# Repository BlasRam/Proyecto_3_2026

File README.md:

# Sistema Experimental para el Monitoreo de la Calidad del Aire Interior (IAQ) y Variables Ambientales con Comunicación LoRa

## Descripción

Este repositorio contiene el desarrollo de un sistema experimental para el monitoreo de la calidad del aire interior (IAQ) y variables ambientales, con capacidad de comunicación inalámbrica mediante tecnología LoRa.

El proyecto está orientado al diseño y validación de una plataforma electrónica basada en **ESP32-S3**, integrando sensado ambiental, adquisición de señales, supervisión energética y transmisión de datos. La propuesta busca servir como base para futuras pruebas de hardware, adquisición de datos ambientales y validación de un sistema completo de monitoreo IAQ.

## Objetivo

Desarrollar una plataforma experimental capaz de:

- monitorear variables asociadas a la calidad del aire interior
- adquirir variables ambientales complementarias
- supervisar el estado energético del sistema
- transmitir información de manera inalámbrica mediante LoRa
- servir como base para futuras etapas de validación y escalabilidad

## Características principales

- Microcontrolador **ESP32-S3**
- Monitoreo de calidad del aire interior (**IAQ**)
- Medición de variables ambientales
- Comunicación **LoRa**
- Supervisión de batería y alimentación
- Diseño electrónico propio en desarrollo
- Arquitectura modular y escalable

## Estado del proyecto

Actualmente el proyecto se encuentra en etapa de:

- desarrollo del esquemático electrónico
- selección e integración de componentes
- definición de arquitectura de alimentación y comunicaciones
- preparación para diseño de PCB
- consolidación del prototipo experimental

## Arquitectura general

El sistema contempla los siguientes bloques principales:

- **Unidad de control:** ESP32-S3
- **Sensado ambiental e IAQ:** sensores para calidad del aire y variables ambientales
- **Comunicación inalámbrica:** módulo LoRa
- **Supervisión energética:** monitoreo de batería y consumo
- **Alimentación:** entrada USB, batería recargable y regulación de voltaje
- **Expansión:** puertos auxiliares para futuras integraciones

## Tecnologías y módulos considerados

Dependiendo de la iteración del prototipo, el sistema contempla o evalúa componentes como:

- **ESP32-S3-WROOM-1**
- **RFM95CW** o **RYLR998** para comunicación LoRa
- **ENS160 / AHT2X** para IAQ y variables ambientales
- **ADS1015** para adquisición analógica adicional
- **MAX17048** para monitoreo de batería
- **TP4056** para carga de batería
- reguladores de 3.3 V para alimentación estable del sistema

## Estructura del repositorio

```text
/
├── Software/          # Programacion (Codigos y Pruebas) del proyecto
├── docs/              # Documentación del proyecto
├── hardware/          # Esquemáticos, PCB, librerías y archivos de diseño
├── firmware/          # Código fuente del microcontrolador
├── images/            # Diagramas, capturas y recursos gráficos
├── datasheets/        # Hojas de datos de los componentes utilizados
└── README.md          # Descripción general del proyecto

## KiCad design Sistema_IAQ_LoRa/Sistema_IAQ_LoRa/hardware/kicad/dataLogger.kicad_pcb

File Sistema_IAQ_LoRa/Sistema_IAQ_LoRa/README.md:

# Sistema Experimental para el Monitoreo de la Calidad del Aire Interior (IAQ) y Variables Ambientales con Comunicación LoRa

## Descripción
Este repositorio contiene el desarrollo de un sistema experimental para el monitoreo de la calidad del aire interior (IAQ) y variables ambientales, con capacidad de comunicación inalámbrica mediante tecnología LoRa.

El proyecto está orientado al diseño y validación de una plataforma electrónica basada en ESP32-S3, integrando sensado ambiental, adquisición de señales, supervisión energética y transmisión de datos. La propuesta busca servir como base para futuras pruebas de hardware, adquisición de datos ambientales y validación de un sistema completo de monitoreo IAQ.

## Estructura del repositorio
```text
.
├── docs/                # Documentación del proyecto
├── hardware/            # Esquemáticos, PCB, librerías y archivos de fabricación
│   ├── kicad/           # Proyecto principal de KiCad
│   ├── libraries/       # Footprints, símbolos y modelos 3D adicionales
│   └── manufacturing/   # Archivos de producción (Gerbers, BOM, posiciones, etc.)
├── firmware/            # Código fuente del microcontrolador
├── images/              # Diagramas, capturas y recursos gráficos
├── datasheets/          # Hojas de datos de los componentes utilizados
└── README.md            # Descripción general del proyecto
```

## Integrantes
- Blas Antonio Ramirez Benitez
- Pedro Daniel Vera Ramirez
- Pablo Junior Otazu Lujan

## Estado del proyecto
Actualmente el proyecto se encuentra en etapa de desarrollo del prototipo electrónico, consolidación del esquemático y organización de los archivos de diseño para futuras pruebas y fabricación.

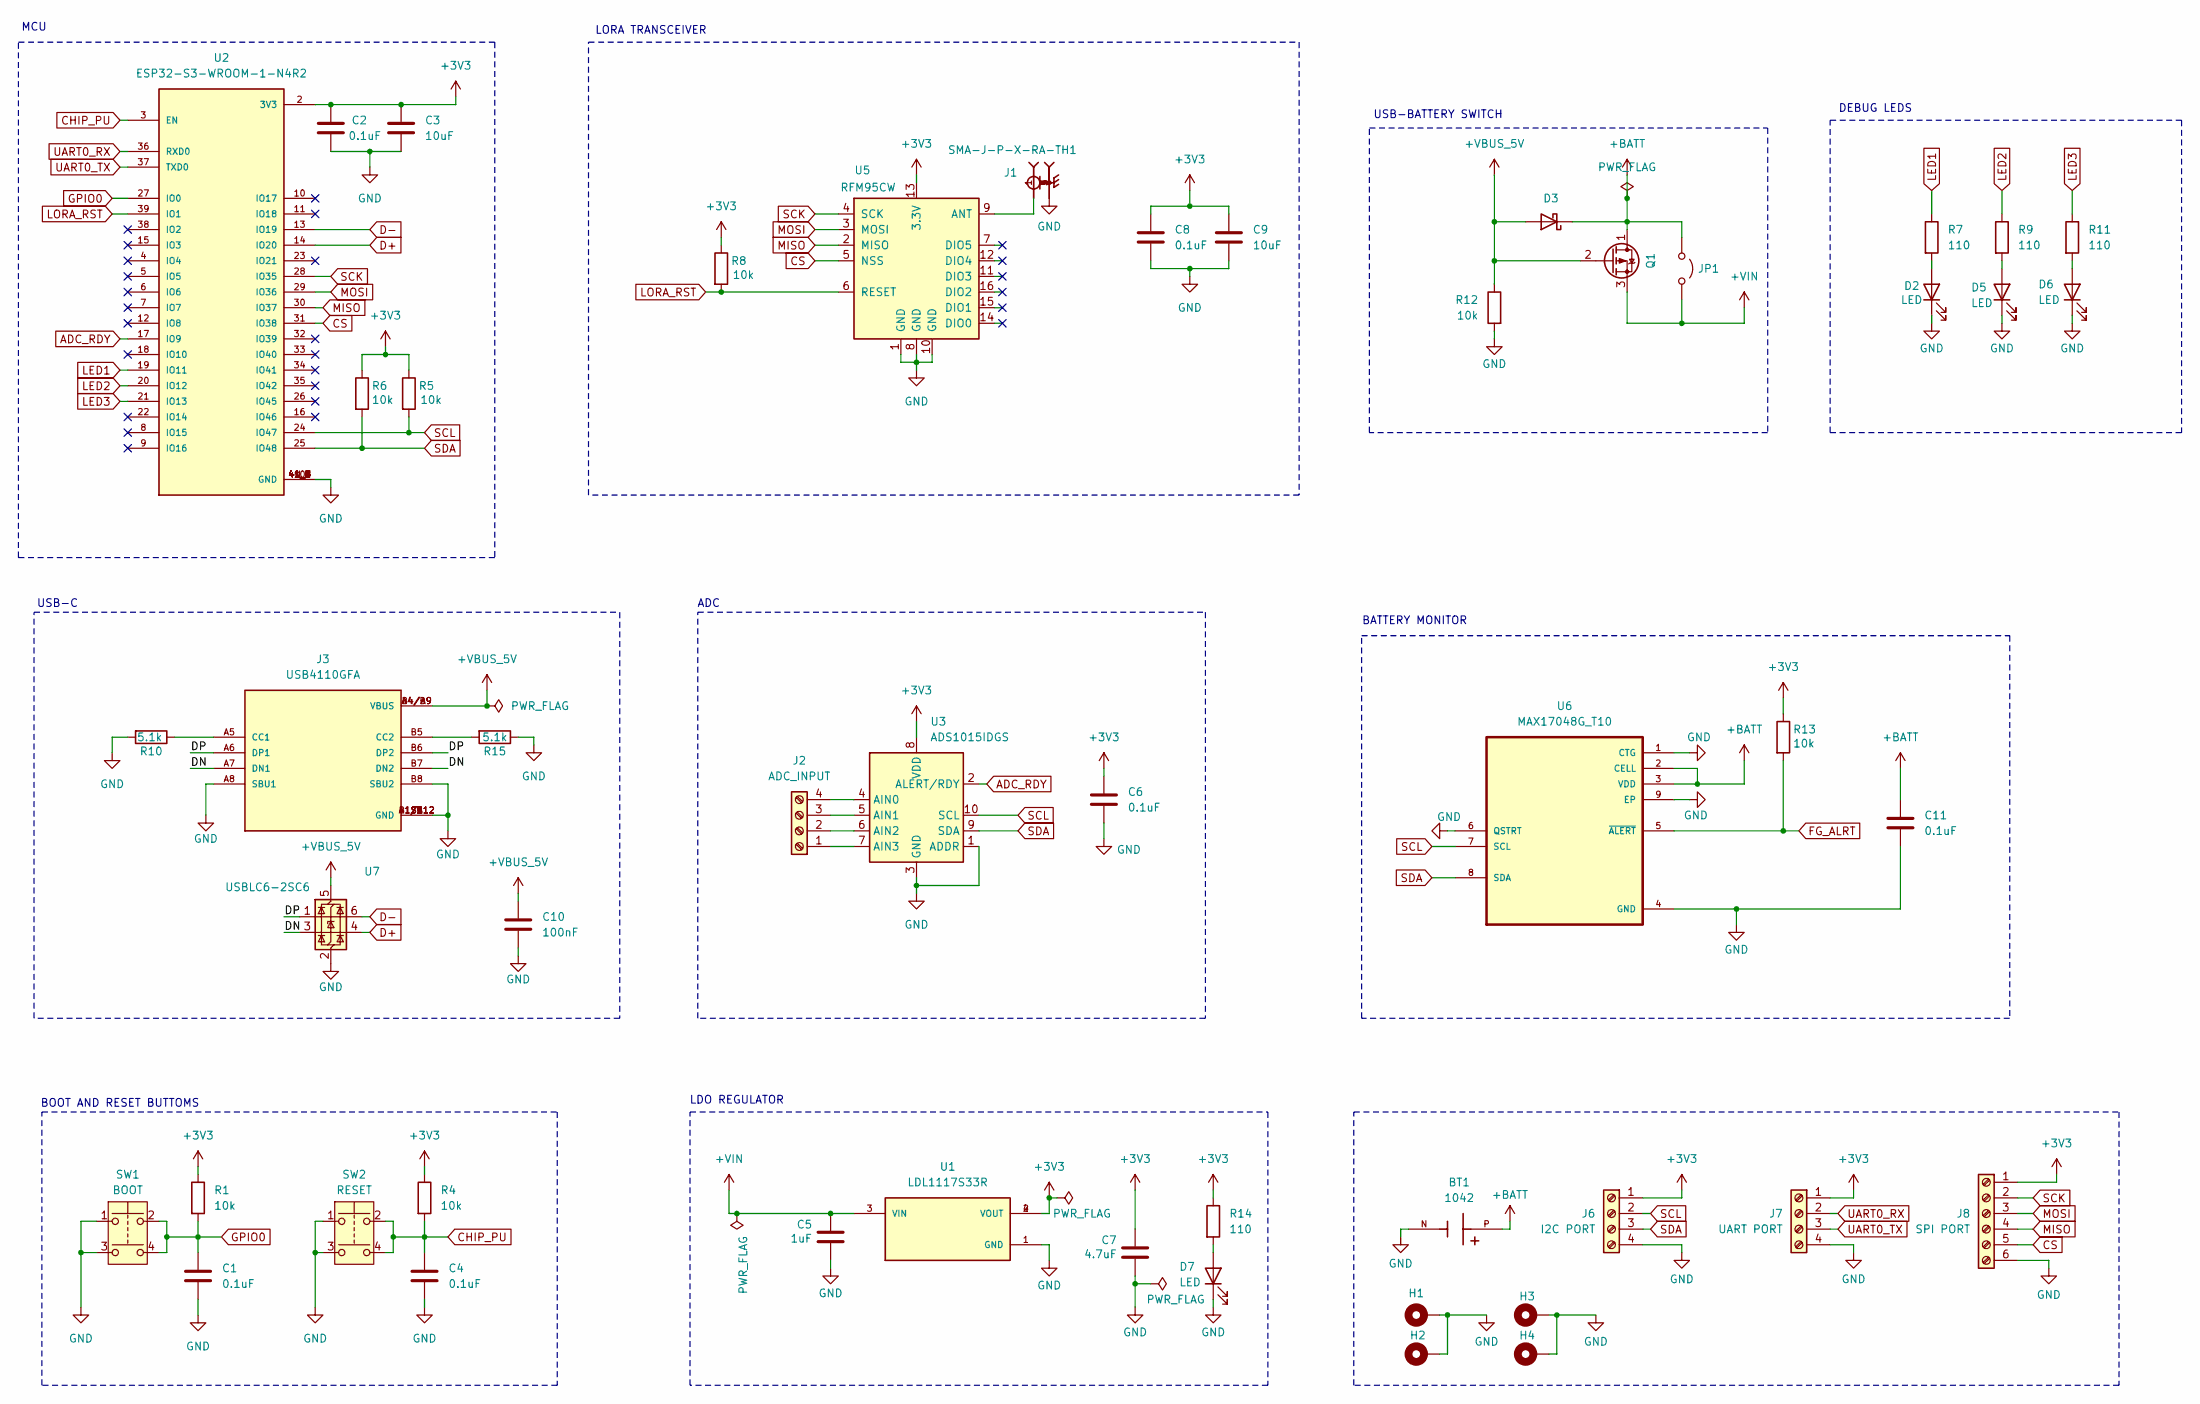
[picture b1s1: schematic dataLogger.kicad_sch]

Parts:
BT1: 1042; BatteryHolder_Keystone_1042_1x18650; PARTREV E
C1, C2, C4, C6, C8, C11: 0.1uF; C_0805_2012Metric
C3, C9: 10uF; C_0805_2012Metric
C5: 1uF; C_0805_2012Metric
C7: 4.7uF; C_0805_2012Metric
C10: 100nF; C_0805_2012Metric
D2, D5, D6, D7: LED; LED_0805_2012Metric
D3: D_Schottky; D_0805_2012Metric
H1, H2, H3, H4: MountingHole_Pad; MountingHole_3.2mm_M3_DIN965_Pad
J1: SMA-J-P-X-RA-TH1; SAMTEC_SMA-J-P-X-RA-TH1; PARTREV K
J2: ADC_INPUT; TerminalBlock_Phoenix_MKDS-1,5-4-5.08_1x04_P5.08mm_Horizont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
J3: USB4110GFA; GCT_USB4110GFA
J6: I2C PORT; PinHeader_1x04_P2.54mm_Vertical
J7: UART PORT; PinHeader_1x04_P2.54mm_Vertical
J8: SPI PORT; PinHeader_1x06_P2.54mm_Vertical
JP1: Jumper_2_Open; SolderJumper-2_P1.3mm_Open_TrianglePad1.0x1.5mm
Q1: Q_PMOS_DGS; SOT-23
R1, R4, R5, R6, R8, R12, R13: 10k; R_0805_2012Metric
R7, R9, R11, R14: 110; R_0805_2012Metric
R10, R15: 5.1k; R_0805_2012Metric
SW1: BOOT; SW_TS04-66-43-BK-100-SMT
SW2: RESET; SW_TS04-66-43-BK-100-SMT
U1: LDL1117S33R; SOT230P700X180-4N; PARTREV 7
U2: ESP32-S3-WROOM-1-N4R2; XCVR_ESP32-S3-WROOM-1-N4R2; PARTREV v1.0
U3: ADS1015IDGS; SOP50P490X110-10N
U5: RFM95CW; XCVR_RFM95W-868S2
U6: MAX17048G_T10; SON50P200X200X80-9N
U7: USBLC6-2SC6; SOT95P280X145-6N

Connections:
+3V3: C2.1, C3.1, C6.1, C7.1, C8.1, C9.1, J6.1, J7.1, J8.1, R1.1, R4.1, R5.1, R6.1, R8.1, R13.1, R14.1, U1.2 (VOUT), U1.4 (VOUT), U2.2 (3V3), U3.8 (VDD), U5.13 (3.3V)
+BATT: BT1.P, C11.1, D3.1 (K), JP1.1 (A), Q1.1 (D), U6.2 (CELL), U6.3 (VDD)
+VBUS_5V: C10.1, D3.2 (A), J3.A4/B9 (VBUS), J3.B4/A9 (VBUS), Q1.2 (G), R12.1, U7.5 (VBUS)
+VIN: C5.1, JP1.2 (B), Q1.3 (S), U1.3 (VIN)
/DN: J3.A7 (DN1), J3.B7 (DN2), U7.3 (I/O2)
/DP: J3.A6 (DP1), J3.B6 (DP2), U7.1 (I/O1)
ADC_RDY: U2.17 (IO9), U3.2 (ALERT/RDY)
CHIP_PU: C4.1, R4.2, SW2.2, SW2.4, U2.3 (EN)
CS: J8.5, U2.31 (IO38), U5.5 (NSS)
D+: U2.14 (IO20), U7.4 (I/O2)
D-: U2.13 (IO19), U7.6 (I/O1)
FG_ALRT: R13.2, U6.5 (~ALERT)
GND: BT1.N, C1.2, C2.2, C3.2, C4.2, C5.2, C6.2, C7.2, C8.2, C9.2, C10.2, C11.2, D2.1 (K), D5.1 (K), D6.1 (K), D7.1 (K), H1.1, H2.1, H3.1, H4.1, J1.2, J1.3, J1.4, J1.5, J3.A1/B12 (GND), J3.A8 (SBU1), J3.B1/A12 (GND), J3.B8 (SBU2), J3.S1 (GND), J3.S2 (GND), J3.S3 (GND), J3.S4 (GND), J6.4, J7.4, J8.6, R10.2, R12.2, R15.1, SW1.1, SW1.3, SW2.1, SW2.3, U1.1 (GND), U2.1 (GND), U2.40 (GND), U2.41_1 (GND), U2.41_2 (GND), U2.41_3 (GND), U2.41_4 (GND), U2.41_5 (GND), U2.41_6 (GND), U2.41_7 (GND), U2.41_8 (GND), U2.41_9 (GND), U3.1 (ADDR), U3.3 (GND), U5.1 (GND), U5.8 (GND), U5.10 (GND), U6.1 (CTG), U6.4 (GND), U6.6 (QSTRT), U6.9 (EP), U7.2 (GND)
GPIO0: C1.1, R1.2, SW1.2, SW1.4, U2.27 (IO0)
LED1: R7.1, U2.19 (IO11)
LED2: R9.1, U2.20 (IO12)
LED3: R11.1, U2.21 (IO13)
LORA_RST: R8.2, U2.39 (IO1), U5.6 (RESET)
MISO: J8.4, U2.30 (IO37), U5.2 (MISO)
MOSI: J8.3, U2.29 (IO36), U5.3 (MOSI)
unnamed: D2.2 (A), R7.2
unnamed: D5.2 (A), R9.2
unnamed: D6.2 (A), R11.2
unnamed: D7.2 (A), R14.2
unnamed: J2.1, U3.7 (AIN3)
unnamed: J2.2, U3.6 (AIN2)
unnamed: J2.3, U3.5 (AIN1)
unnamed: J2.4, U3.4 (AIN0)
unnamed: J3.A5 (CC1), R10.1
unnamed: J3.B5 (CC2), R15.2
unnamed: J1.1, U5.9 (ANT)
SCK: J8.2, U2.28 (IO35), U5.4 (SCK)
SCL: J6.2, R5.2, U2.24 (IO47), U3.10 (SCL), U6.7 (SCL)
SDA: J6.3, R6.2, U2.25 (IO48), U3.9 (SDA), U6.8 (SDA)
UART0_RX: J7.2, U2.36 (RXD0)
UART0_TX: J7.3, U2.37 (TXD0)

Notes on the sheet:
USB-C
LDO REGULATOR
USB-BATTERY SWITCH
BATTERY MONITOR
LORA TRANSCEIVER
BOOT AND RESET BUTTOMS
DEBUG LEDS
MCU
ADC

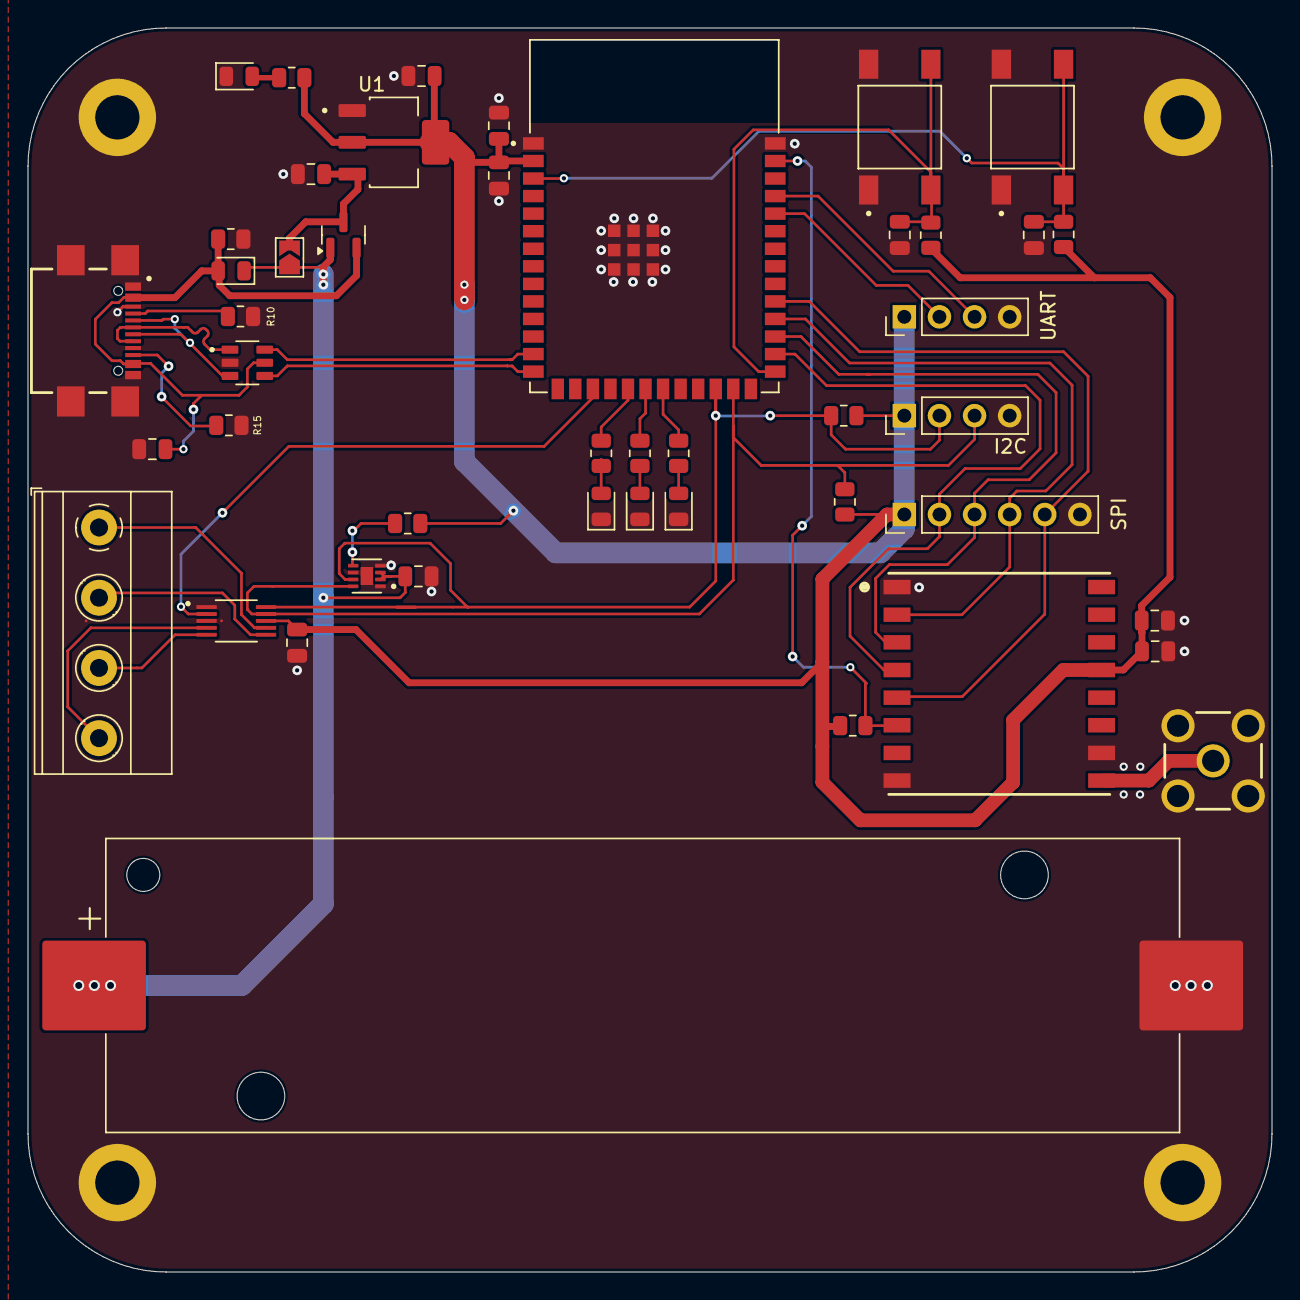
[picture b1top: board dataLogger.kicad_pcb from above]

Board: 2 copper layers, 90.0 x 90.0 mm, 50 parts (0 on the bottom side), 36 nets.
